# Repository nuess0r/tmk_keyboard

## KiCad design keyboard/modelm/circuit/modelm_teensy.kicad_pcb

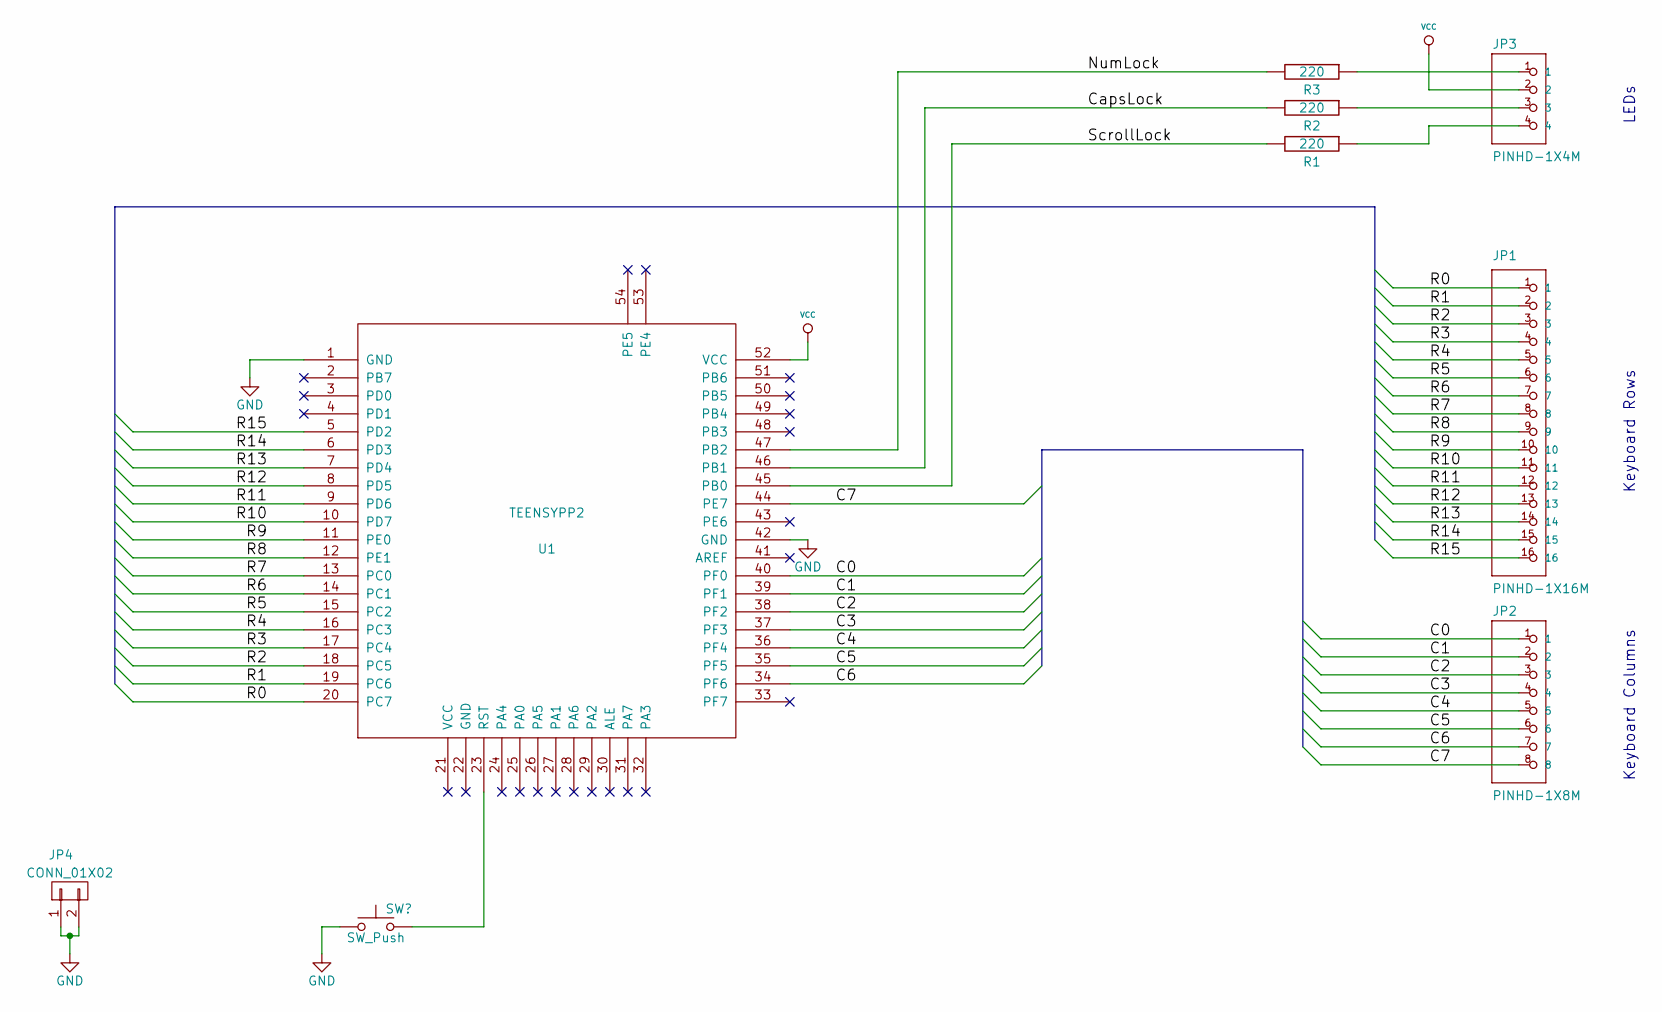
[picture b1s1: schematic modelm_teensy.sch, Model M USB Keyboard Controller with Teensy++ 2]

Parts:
JP1: PINHD-1X16M; Pin_Header_Straight_1x16
JP2: PINHD-1X8M; Pin_Header_Straight_1x08
JP3: PINHD-1X4M; Pin_Header_Straight_1x04
JP4: CONN_01X02; AK300-2
R1, R2, R3: 220; Resistor_Horizontal_RM15mm
U1: TEENSYPP2

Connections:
/C0: JP2.1, U1.40 (PF0)
/C1: JP2.2, U1.39 (PF1)
/C2: JP2.3, U1.38 (PF2)
/C3: JP2.4, U1.37 (PF3)
/C4: JP2.5, U1.36 (PF4)
/C5: JP2.6, U1.35 (PF5)
/C6: JP2.7, U1.34 (PF6)
/C7: JP2.8, U1.44 (PE7)
/CapsLock: R2.2, U1.46 (PB1)
/NumLock: R3.2, U1.47 (PB2)
/R0: JP1.1, U1.20 (PC7)
/R1: JP1.2, U1.19 (PC6)
/R2: JP1.3, U1.18 (PC5)
/R3: JP1.4, U1.17 (PC4)
/R4: JP1.5, U1.16 (PC3)
/R5: JP1.6, U1.15 (PC2)
/R6: JP1.7, U1.14 (PC1)
/R7: JP1.8, U1.13 (PC0)
/R8: JP1.9, U1.12 (PE1)
/R9: JP1.10, U1.11 (PE0)
/R10: JP1.11, U1.10 (PD7)
/R11: JP1.12, U1.9 (PD6)
/R12: JP1.13, U1.8 (PD5)
/R13: JP1.14, U1.7 (PD4)
/R14: JP1.15, U1.6 (PD3)
/R15: JP1.16, U1.5 (PD2)
/ScrollLock: R1.2, U1.45 (PB0)
GND: JP4.1, JP4.2, U1.1 (GND), U1.42 (GND); also elsewhere on the board
unnamed: JP3.1, R3.1
unnamed: JP3.3, R2.1
unnamed: JP3.4, R1.1
unnamed 31: U1.23 (RST); also elsewhere on the board
VCC: JP3.2, U1.52 (VCC)

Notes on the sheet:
Keyboard Rows
Keyboard Columns
LEDs

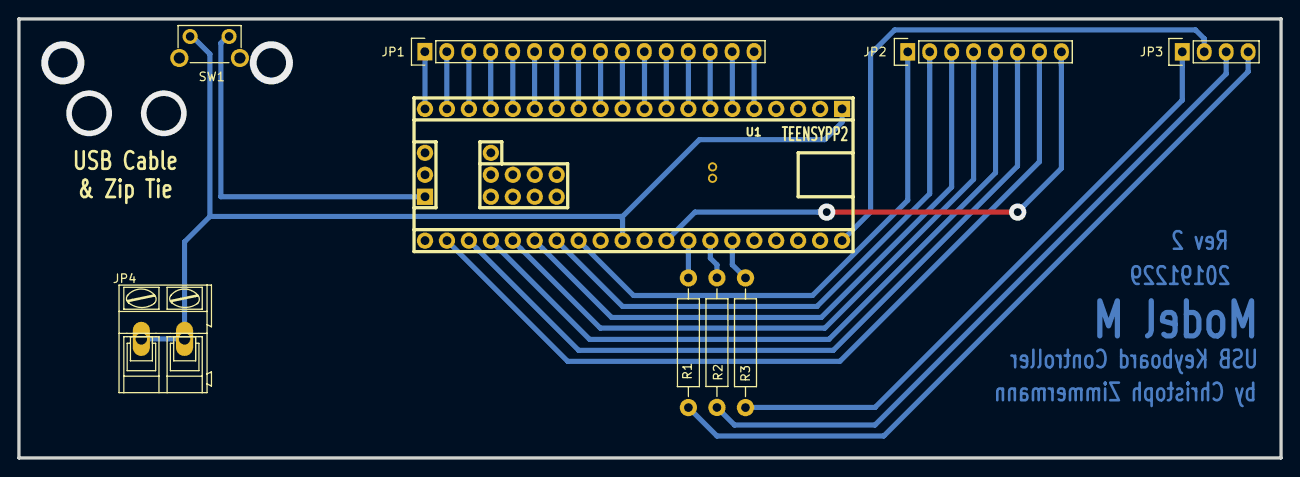
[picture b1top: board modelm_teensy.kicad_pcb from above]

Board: 2 copper layers, 146.0 x 50.8 mm, 9 parts (0 on the bottom side), 33 nets.

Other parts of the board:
SW1: Reset; SW_Tactile_SPST_Angled

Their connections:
GND: SW1.1; also elsewhere on the board
unnamed 31: SW1.2; also elsewhere on the board

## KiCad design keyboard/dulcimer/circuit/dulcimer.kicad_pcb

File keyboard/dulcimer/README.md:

USB Controller for a IBM Model M Keyboard
=========================================

This is a port of the TMK firmware to the dulcimer project.

The dulcimer project is a USB replacement controller for the IBM Model M keyboard.

You can find the original documentation here:
http://www.schatenseite.de/2008/07/12/dulcimer/

This controller uses an ATmega32 and the VUSB library for USB support.

If you happen to have a Teensy 2.0++ lying around, you can use a different port
of TMK to make your beloved Model M future proof:
https://blog.lmorchard.com/2016/02/21/modelm-controller/ (Thanks to Les Orchard
for all the work to create the Model M keymap)

Keymaps
-------

By default this TMK firmware provides a classical QUERTY layout for 101/103 keys.

The project provides an additional modernized keymap with multimedia keys.
See Building Yourself how to build the firmware with this optional mappings.

In the variant keymap_modernized.c some keys are
remapped to more modern use cases:
- Caps lock is now Windows Key or Command key in Mac
- F11 is now Media Play
- F12 is now Media Next
- Print Screen is now Volume Mute
- Scroll lock is now Volume up
- Break is now Volume down

Boot Magic Configuration - Virtual DIP Switch
---------------------------------------------
Boot Magic are executed during boot up time. Press Magic key below then plug in keyboard cable.
Note that you must use keys of **Layer 0** as Magic keys. These settings are stored in EEPROM so that retain your configure over power cycles.

To avoid configuring accidentally additive salt key `KC_INS` also needs to be pressed along with the following configuration keys. The salt key on the Model M is `insert` instead of the TMK default `space`!

#### General
- Skip reading EEPROM to start with default configuration(`ESC`)
- Clear configuration stored in EEPROM to reset configuration(`Backspace`)

#### Bootloader
- Kick up Bootloader(`B`)

#### Debug
- Debug enable(`D`)
- Debug matrix enable(`D`+`X`)
- Debug keyboard enable(`D`+`K`)
- Debug mouse enable(`D`+`M`)

#### Keymap
- Swap Control and CapsLock(`Left Control`)
- Change CapsLock to Control(`Caps Lock`)
- Swap LeftAlt and Gui(`Left Alt`)
- Swap RightAlt and Gui(`Right Alt`)
- Disable Gui(`Left Gui`)
- Swap Grave and Escape(`Grave`)
- Swap BackSlash and BackSpace(`Back Slash`)
- Enable NKRO on boot(`N`)

#### Default Layer
- Set Default Layer to 0(`0`)
- Set Default Layer to 1(`1`)
- Set Default Layer to 2(`2`)
- Set Default Layer to 3(`3`)
- Set Default Layer to 4(`4`)
- Set Default Layer to 5(`5`)
- Set Default Layer to 6(`6`)
- Set Default Layer to 7(`7`)

Hardware
---------

You can use the original dulcimer hardware without modification with
this TMK firmware.

If you don't own one, you can build one yourself. In the circuit sub-folder
is a KiCAD project for the dulcimer.

It's a one layer PCB, so you can either etch your self a PCB or order a PCB
from yourfavorite manufacturer.

Firmware
--------

The firmware consists of two parts, the bootloader and the actual TMK firmware.

Building Firmware Yourself
--------------------------

You need to install avr-gcc, the avr glibc and avrdude.

### Bootloader

Enter the bootloader directory and execute

    make

Use avrdude with your programmer settings adjusted:

    avrdude -P /dev/ttyACM0 -c STK500 -p atmega32 -U flash:w:obj/main.hex -U hfuse:w:0xc8:m -U lfuse:w:0x8f:m

    avrdude -c dragon_isp -B 5 -p atmega32 -U flash:w:obj/main.hex -U hfuse:w:0xc8:m -U lfuse:w:0x8f:m

### TMK Firmware

After you flashed the bootloader you can make and flash the TMK firmware.

Before you build it, you have to decide which keymap you would like to use.

Rename the desired keymap file to `keymap.c` and build the firmware:

    make

The bootloader is loaded only for a few seconds before the TMK firmware gets loaded.
Flash the firwmare during this short period with a simple:

    make program

or use again avrdude with the settings adjusted for the usbasp bootloader:

    avrdude -p atmega32 -P /dev/ttyACM0 -c usbasp -U flash:w:dulcimer.hex -U lfuse:w:0x8F:m -U hfuse:w:0xC8:m

Debugging
---------

Debugging is done via the serial UART in the AVR. No debugging messages are transferred via USB.

The transmit pin (TX) is available on the connector JP4.

It is 5 V TTL, so you will need a RS232 level shifter or a 5 V tolerant USB
serial adapter (you can use two resistors to build a voltage divider to
protect your 3.3 V tolerant adapter)

You have to set `NO_UART = no` in the Makefile and after flashing you can enable
the debug messages by pressing the magic command `LShift` + `RShift` + `d`

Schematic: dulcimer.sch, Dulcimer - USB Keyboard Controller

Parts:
C1: 100n; C_Rect_L4_W2.5_P2.5
C2: 10u; C_Radial_D5_L11_P2.5
C3, C4: 22p; C_Disc_D3_P2.5
D1, D2: 3.6V; D3
IC1: MEGA32-P; DIP-40_W15.24mm_LongPads
JP1: PINHD-1X16M; Pin_Header_Straight_1x16
JP2: PINHD-1X8M; Pin_Header_Straight_1x08
JP3: PINHD-1X4M; Pin_Header_Straight_1x04
JP4, JP5, JP6: JUMPER; Pin_Header_Straight_1x02
JP7: CONN_02X03; Pin_Header_Straight_2x03
JP8: CONN_01X02; AK300-2
JP9: USB; CONN_USB-B
R1: 10k; Resistor_Horizontal_RM10mm
R2: 2k2; Resistor_Horizontal_RM10mm
R3, R4, R5: 470; Resistor_Horizontal_RM10mm
R7, R8: 68; Resistor_Horizontal_RM10mm
X1: 12MHz; Crystal_HC49-U_Vertical

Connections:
/C0: IC1.1, JP2.1
/C1: IC1.2, JP2.2
/C2: IC1.3, JP2.3
/C3: IC1.4, JP2.4
/C4: IC1.5, JP2.5
/C5: IC1.6, JP2.6, JP7.4
/C6: IC1.7, JP2.7, JP7.1
/C7: IC1.8, JP2.8, JP7.3
/CapsLock: IC1.19, R4.2
/NumLock: IC1.20, R3.2
/R0: IC1.40, JP1.1
/R1: IC1.39, JP1.2
/R2: IC1.38, JP1.3
/R3: IC1.37, JP1.4
/R4: IC1.36, JP1.5
/R5: IC1.35, JP1.6
/R6: IC1.34, JP1.7
/R7: IC1.33, JP1.8
/R8: IC1.29, JP1.9
/R9: IC1.28, JP1.10
/R10: IC1.27, JP1.11
/R11: IC1.26, JP1.12
/R12: IC1.25, JP1.13
/R13: IC1.24, JP1.14
/R14: IC1.23, JP1.15
/R15: IC1.22, JP1.16
/Reset: IC1.9, JP7.5, R1.1
/ScrollLock: IC1.18, R5.2
Earth: JP8.1, JP8.2, JP9.6
GND: C1.1, C2.1, C3.2, C4.2, D1.1 (A), D2.1 (A), IC1.11, JP4.2, JP5.2, JP6.2, JP7.6, JP9.4
unnamed: C3.1, IC1.12, X1.1
unnamed: C4.1, IC1.13, X1.2
unnamed: D1.2 (K), JP9.2, R2.2, R8.1
unnamed: D2.2 (K), JP9.3, R7.1
unnamed: IC1.14, R8.2
unnamed: IC1.15, JP4.1
unnamed: IC1.16, R7.2
unnamed: IC1.17, JP5.1
unnamed: IC1.21, JP6.1
unnamed: JP3.1, R3.1
unnamed: JP3.3, R4.1
unnamed: JP3.4, R5.1
VCC: C1.2, C2.2, IC1.10, JP3.2, JP7.2, JP9.1, R1.2, R2.1

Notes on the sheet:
Keyboard Rows
Keyboard Columns
LEDs
ISP
These jumpers are optional. Not used in TMK or dulcimer firmware.

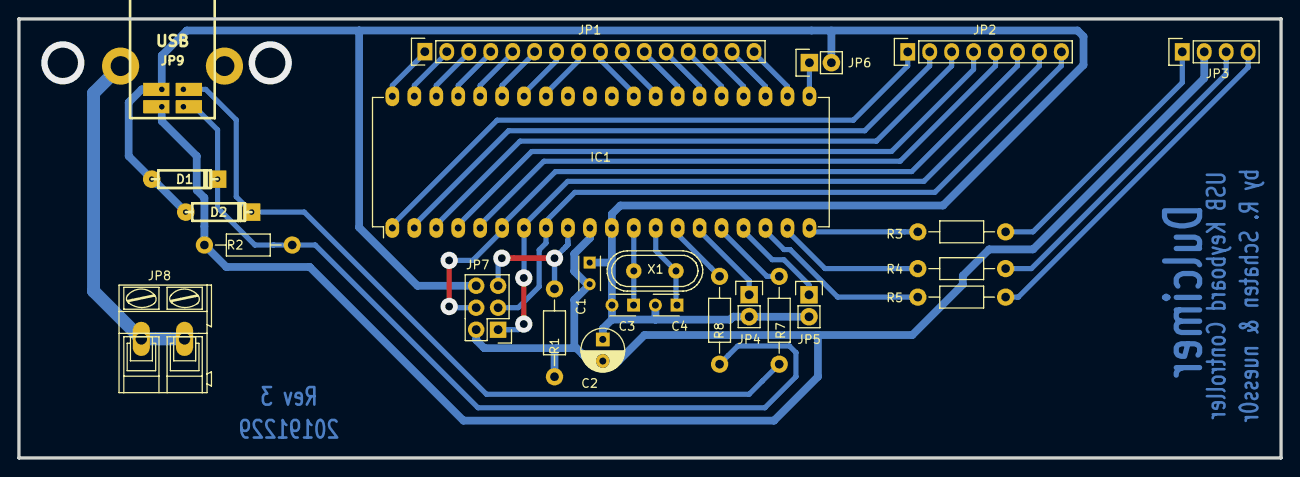
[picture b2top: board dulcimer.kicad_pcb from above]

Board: 2 copper layers, 146.0 x 50.8 mm, 24 parts (0 on the bottom side), 43 nets.

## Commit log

2016-06-24 Initial working breadboard for Model M
2016-06-24 Swap matrix rows & columns, wire up the LEDs, play with ghosting
2016-06-24 Rework pin layout to reflect rewiring that fits in Model M case
2016-06-24 Ignore VIM swapfiles
2016-06-24 Switch from D6 (with built-in LED) to D0
2016-06-24 Tweak keymap for Mac
2018-03-28 Removed unused code that breaks compilation with ATMEGA32
2018-03-28 Revert "Removed unused code that breaks compilation with ATMEGA32"
2018-03-29 Small patch to make it compile with recent TMK and avr-gcc version.
2018-04-03 Initial commit of the port to the dulcimer controller board (USB interface for IBM Model M).
    It compiles but does not link sugessfully.
2018-04-03 Added finished and tested KiCAD project incl. Gerber exports.
    Compared to the original Dulcimer board the newer 6 pin ISP connecter is used and the jumpers to debug the USB connection are removed.
2018-04-03 made it more portable by using the existing TIMSK0 define.
2018-04-05 little clean up
2018-04-05 Modified tmk_core/avr to be able to select more registers to use at compile time like it is already done with TIMSK/TIMSK0. This was needed to port tmk to an atmega32.
2018-04-05 Use of new defines in tmk_core to compile it for atmega32.
2018-04-07 added missing project file and a KiCAD tailored gitignore file.
2018-04-07 PCB design for the Teensy++ 2.0 based IBM Model M USB controller supporting the TMK firmware.
2018-04-12 First working version. Needs more testing and bootloader is missing.
2018-07-08 Added modified hid_listen tool to read debug messages on the host sent by the dulcimer TMK firmware
2018-07-09 Added bootloader.
    We use the usbasp bootloader. Configured for and sucessfully tested on the dulcimer hardware.
    Also including the working binary (obj/main.hex)
2018-07-09 Changed Makefile to use the usbasp bootloader which is now working on the dulcimer
2019-12-29 Corrected the orientation of the LED connector
    Fixes after first prototypes where built:
    The LED connector was wrongly rotated by 180°. This is corrected now.
    Added drawing on how to mount the compontents to the PCB
2019-12-29 Corrected LED connector orientation
    The connector for the LEDs was wrongly rotated by 180°. This is fixed now.
2019-12-30 Added README for Model M keyboard
    Commit of current state and includes a README for the port of TMK to the
    dulcimer Model M USB controller.
2019-12-30 Merged upstream changes from tmk repo
2020-01-02 Adding 103 keymap variants
2020-01-02 Changed boot magic salt key to 'insert'
    The salt key on the Model M is `insert` instead of the TMK default `space`!
    The space key conflicts with backspace, insert works fine.
2020-01-02 Disable debugging
2020-01-02 Fix for: VUSB: undefined references #547
    Report keyboard_protocol and keyboard_idle only when they are implemented
2020-01-02 Change VUSB NO_UART check the same style as other Makefile options
    Same yes/no posibility than the other documented options. Before it worked
    when set to yes, but set to no also disabled it.
2020-01-03 Enhanced readme and fixes to modernized keymaps
2020-01-04 merged 101 and 103 key variant
    it is not needed to have separated 101 and 103 keymap variants because they
    don't conflict with each other.
